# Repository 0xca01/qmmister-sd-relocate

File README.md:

# qmmister-sd-relocate
Simple PCB to enable relocation of microSD card slot on the QMTech MiSTer board. Tested and working - recommend 0.6mm board as the minimum stack height to clear the SMD resistors. J1 flex connector on the MiSTer board needs to be removed. A 50mm 9 pin flex cable (0.5mm pitch) connects the two halves.

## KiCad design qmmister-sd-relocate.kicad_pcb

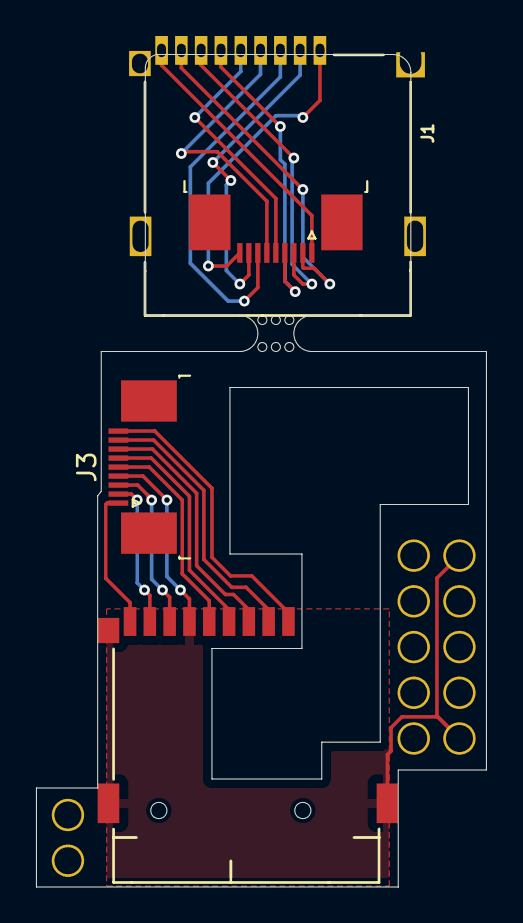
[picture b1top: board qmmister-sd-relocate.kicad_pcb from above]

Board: 2 copper layers, 25.0 x 46.2 mm, 7 parts (0 on the bottom side), 18 nets.

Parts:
J1, J2: Micro_SD_Card_Det1; J_SD_Card-micro_socket_A
J3, J4: Conn_01x09; TE_0-1734839-9_1x09-1MP_P0.5mm_Horizontal
J5: PinHeader_1x02_P2.54mm_Vertical
J6: PinHeader_2x05_P2.54mm_Vertical
mouse-bite-2mm-slot: VAL**; mouse-bite-2mm-slot

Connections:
GND: J2.6 (VSS), J2.SH, J6.1, J6.9
unnamed: J1.5 (CLK), J4.5
unnamed: J1.3 (CMD), J4.7
unnamed: J1.7 (DAT0), J4.3
unnamed: J1.8 (DAT1), J4.2
unnamed: J1.1 (DAT2), J4.9
unnamed: J1.2 (DAT3/CD), J4.8
unnamed: J1.9 (DET), J4.1
unnamed: J1.4 (VDD), J4.6
unnamed: J1.6 (VSS), J4.4
unnamed: J2.5 (CLK), J3.5
unnamed: J2.3 (CMD), J3.7
unnamed: J2.7 (DAT0), J3.3
unnamed: J2.8 (DAT1), J3.2
unnamed: J2.1 (DAT2), J3.9
unnamed: J2.2 (DAT3/CD), J3.8
unnamed: J2.9 (DET), J3.1
unnamed: J2.4 (VDD), J3.6

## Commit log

2024-08-27 Add kicad project files
2024-08-28 Minor tweaks - allow VSS pad to utilize fill zone
